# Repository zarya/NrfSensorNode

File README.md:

NrfSensorNode
=============

This is the software for the NRF24L01 Sensor node see https://gigafreak.net/stats/

* To use this install http://inotool.org/quickstart

# Features
* Serial config menu
* Onewire bus (DS18S20,DS18B20)
* DHT11,DHT21,DHT22,DHT44 Humidity and Temperature sensor
* HTU21D Humidity and Temperature sensor
* BMP085/180 pressure sensor support
* 2 x Interrupt driven pulse inputs
* 8 x Analog pin input
* OTA-Config
* PWM pin control
* IO pin control
* WS2801 ledstrip support

## Wishlist
* Serial camera support

# Structs
## Payload
| name | type | description |
-------|------|-------------|
| type | char | Packet type |
| sensor | uint8 | Sensor ID |
| value | float | Sensor value | 
 
### Packet types

| Type | Description |
-------|-------------|
| T | Temperature |
| H | Humidity |
| P | Pulse |
| A | Analog pin reading |
| P | Ping request |
| Q | Ping reply |
| C | Config data |
| O | Output pin data |
| D | Pressure |

## Config Payload
| name | type | description |
-------|------|-------------|
| pos  | uint8 | posision in the config struct |
| data | uint8 | value |

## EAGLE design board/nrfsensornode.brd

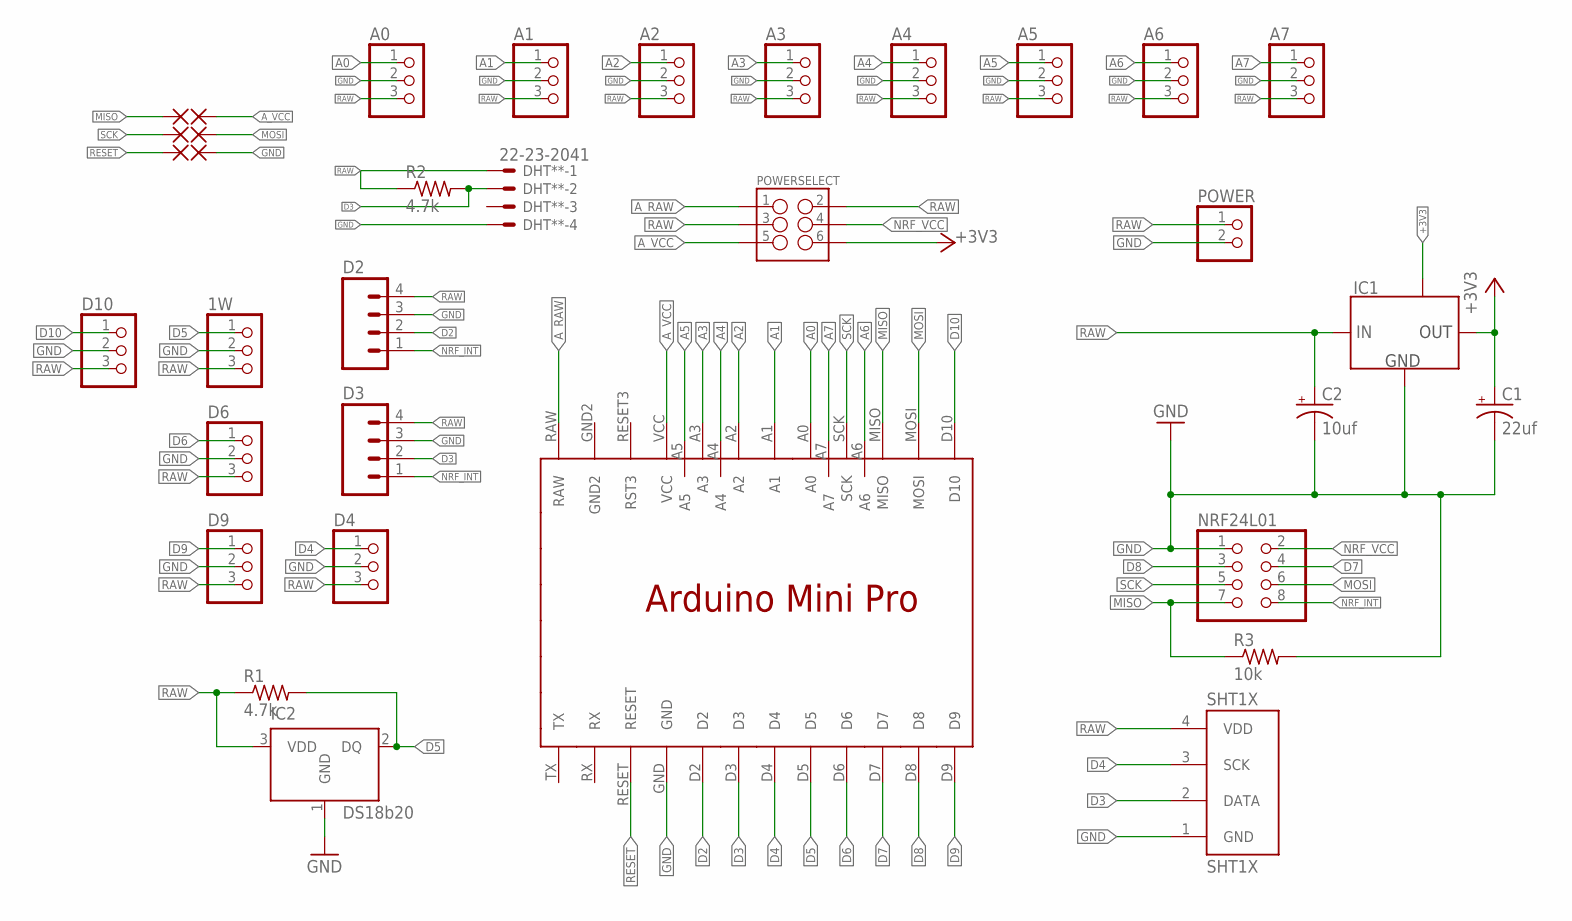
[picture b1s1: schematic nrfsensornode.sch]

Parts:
1W: PINHD-1X3; 1X03
5V: WIREPADSMD1,27-254; SMD1,27-2,54
A0, A1, A2, A3, A4, A5, A6, A7: PINHD-1X3; 1X03
C1: 22uf; E2-4
C2: 10uf; E2-4
D2, D3: M04LOCK; 1X04_LOCK
D4, D6, D9, D10: PINHD-1X3; 1X03
DHT**: 22-23-2041
GND: WIREPADSMD1,27-254; SMD1,27-2,54
IC1: LM1117MPX-3.3; SOT-223
IC2: DS18b20; TO-92
MISO: WIREPADSMD1,27-254; SMD1,27-2,54
MOSI: WIREPADSMD1,27-254; SMD1,27-2,54
NRF24L01: PINHD-2X4; 2X04
POWER: PINHD-1X2; 1X02
POWERSELECT: M03X2POGO_PINS; 2X3_POGO
R1, R2: 4.7k; M1206
R3: 10k; M1206
RST: WIREPADSMD1,27-254; SMD1,27-2,54
SCK: WIREPADSMD1,27-254; SMD1,27-2,54
SHT1X: SHT1X
U$1: ARDMINIPRO

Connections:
+3V3: C1.+, IC1.2 (OUT), IC1.4 (NC), POWERSELECT.P$6 (6)
A0: A0.1, U$1.A0
A1: A1.1, U$1.A1
A2: A2.1, U$1.A2
A3: A3.1, U$1.A3
A4: A4.1, U$1.A4
A5: A5.1, U$1.A5
A6: A6.1, U$1.A6
A7: A7.1, U$1.A7
A_RAW: POWERSELECT.P$1 (1), U$1.RAW
A_VCC: 5V.1, POWERSELECT.P$5 (5), U$1.VCC
D2: D2.2, U$1.D2
D3: D3.2, DHT**.2, R2.2, SHT1X.2 (DATA), U$1.D3
D4: D4.1, SHT1X.3 (SCK), U$1.D4
D5: 1W.1, IC2.2 (DQ), R1.2, U$1.D5
D6: D6.1, U$1.D6
D7: NRF24L01.4, U$1.D7
D8: NRF24L01.3, U$1.D8
D9: D9.1, U$1.D9
D10: D10.1, U$1.D10
GND: 1W.2, A0.2, A1.2, A2.2, A3.2, A4.2, A5.2, A6.2, A7.2, C1.-, C2.-, D2.3, D3.3, D4.2, D6.2, D9.2, D10.2, DHT**.4, GND.1, IC1.1 (GND), IC2.1 (GND), NRF24L01.1, POWER.2, R3.2, SHT1X.1 (GND), U$1.GND
MISO: MISO.1, NRF24L01.7, R3.1, U$1.MISO
MOSI: MOSI.1, NRF24L01.6, U$1.MOSI
NRF_INT: D2.1, D3.1, NRF24L01.8
NRF_VCC: NRF24L01.2, POWERSELECT.P$4 (4)
RAW: 1W.3, A0.3, A1.3, A2.3, A3.3, A4.3, A5.3, A6.3, A7.3, C2.+, D2.4, D3.4, D4.3, D6.3, D9.3, D10.3, DHT**.1, IC1.3 (IN), IC2.3 (VDD), POWER.1, POWERSELECT.P$2 (2), POWERSELECT.P$3 (3), R1.1, R2.1, SHT1X.4 (VDD)
RESET: RST.1, U$1.RESET
SCK: NRF24L01.5, SCK.1, U$1.SCK

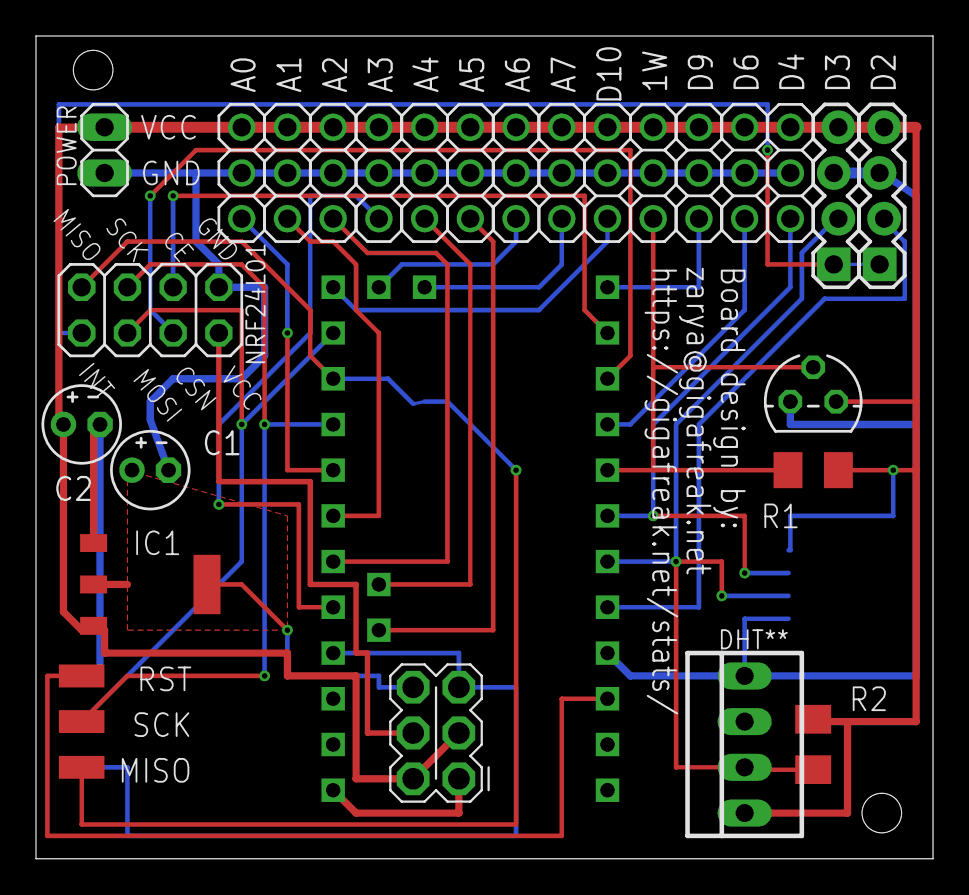
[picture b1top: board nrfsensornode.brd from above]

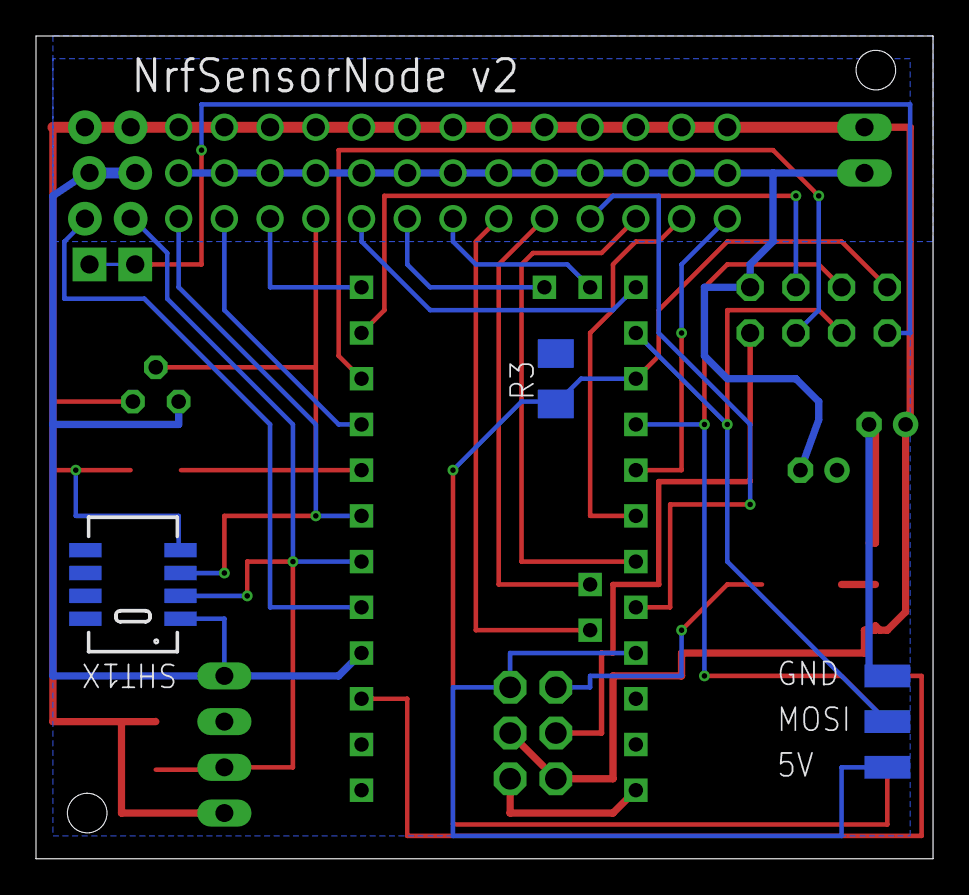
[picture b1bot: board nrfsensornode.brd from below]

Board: 2 copper layers, 49.8 x 45.7 mm, 35 parts (5 on the bottom side), 28 nets.

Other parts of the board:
U$2: OSHWLOGO_TOL_0.2

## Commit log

2014-01-26 Initial import to git
2014-01-26 Code cleanup
2014-01-26 Made option to disable config menu
2014-01-26 Cleanup the menu code, added config option for p[0-1] debouce
2014-01-26 Fix for debounce config value
2014-01-27 Added DHT11/21/22 support
2014-01-27 made onewire module enabe/disable
2014-01-28 Added analog config menu, added some input validation, some cleanups
2014-01-28 Added comments and did a cleanup of unused vars
2014-01-31 Large change for negative numbers
2014-02-01 Added debugging options, added nodeid mapping
2014-02-01 Added description
2014-02-01 Update node_id_mapping
2014-02-01 String cleanup
2014-02-01 Fixed bug in readDHTSensor
2014-02-02 Cleanup
2014-02-02 Code cleanup compile size is now 23954 byes
2014-02-02 Some more cleanups
2014-02-02 Moved things to header files, cleaned up some strings size is now 23922 bytes
2014-02-02 More clean up size: 23888 bytes
2014-02-03 Added OTA-Config support
2014-02-03 Added ota load payload
2014-02-03 Fixed typo
2014-02-09 Added EAGLE Schema
2014-02-17 Added pin output support
2014-02-18 Replaced the dht lib
2014-03-31 Various changes
2014-05-10 updates and bugfixes
2014-05-10 Added factory reset function (clear)
2014-05-10 Update to battery monitor
2014-05-18 updated libs updated board
2014-06-24 Updates \o/
2014-07-12 * Added new DHT lib from https://github.com/RobTillaart/Arduino/blob/master/libraries/DHTlib * Added Adafruit sensor lib * Added Adafruit BMP lib * Added support for DHT44 * Added support for BMP085/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
2014-07-18 Added support for the HTU21D temperature and humidity sensor
2014-07-24 Fixed DHT precision, cleaned some code
2014-08-01 changed case for dht.h
2014-08-02 fixed the DHT lib
2014-08-02 fixed the case (again)
2014-08-02 a nother case fix
2014-08-05 small changes
2014-08-06 Moving some stuff arround
2014-08-06 added DHT readme back in
2014-08-06 added install script to fix libs
2014-08-06 Moved most of the libs to submodules
2014-08-06 updated install.sh, moved RF24 to submodule
2014-08-06 Fixed readBMP
2014-08-07 fixed ws2801 driver
2014-08-11 Changed sensor payload value from int16 to float. This requires update of all the nodes and code
2014-08-15 Added AS3935 lib
2014-08-16 Updated submodules
2014-08-18 Code refactor
2014-09-19 Updated libs and added software pull-up for interrupts
2015-01-25 Fixed 1wire temperature bug

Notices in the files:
parts and their libraries:
SparkFun-Connectors: Licensing: Creative Commons ShareAlike 4.0 International - https://creativecommons.org/licenses/by-sa/4.0
